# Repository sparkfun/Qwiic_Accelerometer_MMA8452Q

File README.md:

Qwiic Accelerometer - MMA8452Q
========================================

[*SEN-14587*](https://www.sparkfun.com/products/14587)

The Qwiic Accelerometer makes it extremely easy to get playing with tilt, acceleration, and movement sensing. Plug a [Qwiic Shield](https://www.sparkfun.com/search/results?term=qwiic) onto your platform of choice, plug the Qwiic Accelerometer onto the shield and start sensing! 

The Qwiic Accelerometer - MMA8452Q is a smart low-power, three-axis, MEMS accelerometer with 12 bits of resolution. This accelerometer is packed with embedded functions with flexible user programmable options, configurable to two interrupt pins. Embedded interrupt functions allow for overall power savings relieving the host processor from continuously polling data.

The MMA8452Q has user selectable full scales of ±2g/±4g/±8g with high pass filtered data as well as non filtered data available real-time. The device can be configured to generate inertial wake-up interrupt signals from any combination of the configurable embedded functions allowing the MMA8452Q to monitor events and remain in a low power mode during periods of inactivity.

Documentation
--------------
* **Library GitHub Repo**
  * **[Arduino Library](https://github.com/sparkfun/SparkFun_MMA8452Q_Arduino_Library/tree/master)** - Arduino library for MMA8452Q.
  * **[Photon Library](https://github.com/sparkfun/SparkFun_MMA8452Q_Particle_Library)** - Photon library for MMA8452Q.
* **[Hookup Guide](https://learn.sparkfun.com/tutorials/qwiic-accelerometer-mma8452q-hookup-guide)** - Basic hookup guide for the MMA8452Q Breakout Board.
* **[Qwiic System](http://www.sparkfun.com/qwiic)** - The Qwiic system enables fast and solderless connection between popular platforms and various sensors and actuators.

Product Versions
----------------
* [SEN-14587](https://www.sparkfun.com/products/14587)
* [SPX-14248](https://www.sparkfun.com/products/14248)

License Information
-------------------

This product is _**open source**_!

Please review the LICENSE.md file for license information.

If you have any questions or concerns on licensing, please contact techsupport@sparkfun.com.

Distributed as-is; no warranty is given.

- Your friends at SparkFun.

_<COLLABORATION CREDIT>_

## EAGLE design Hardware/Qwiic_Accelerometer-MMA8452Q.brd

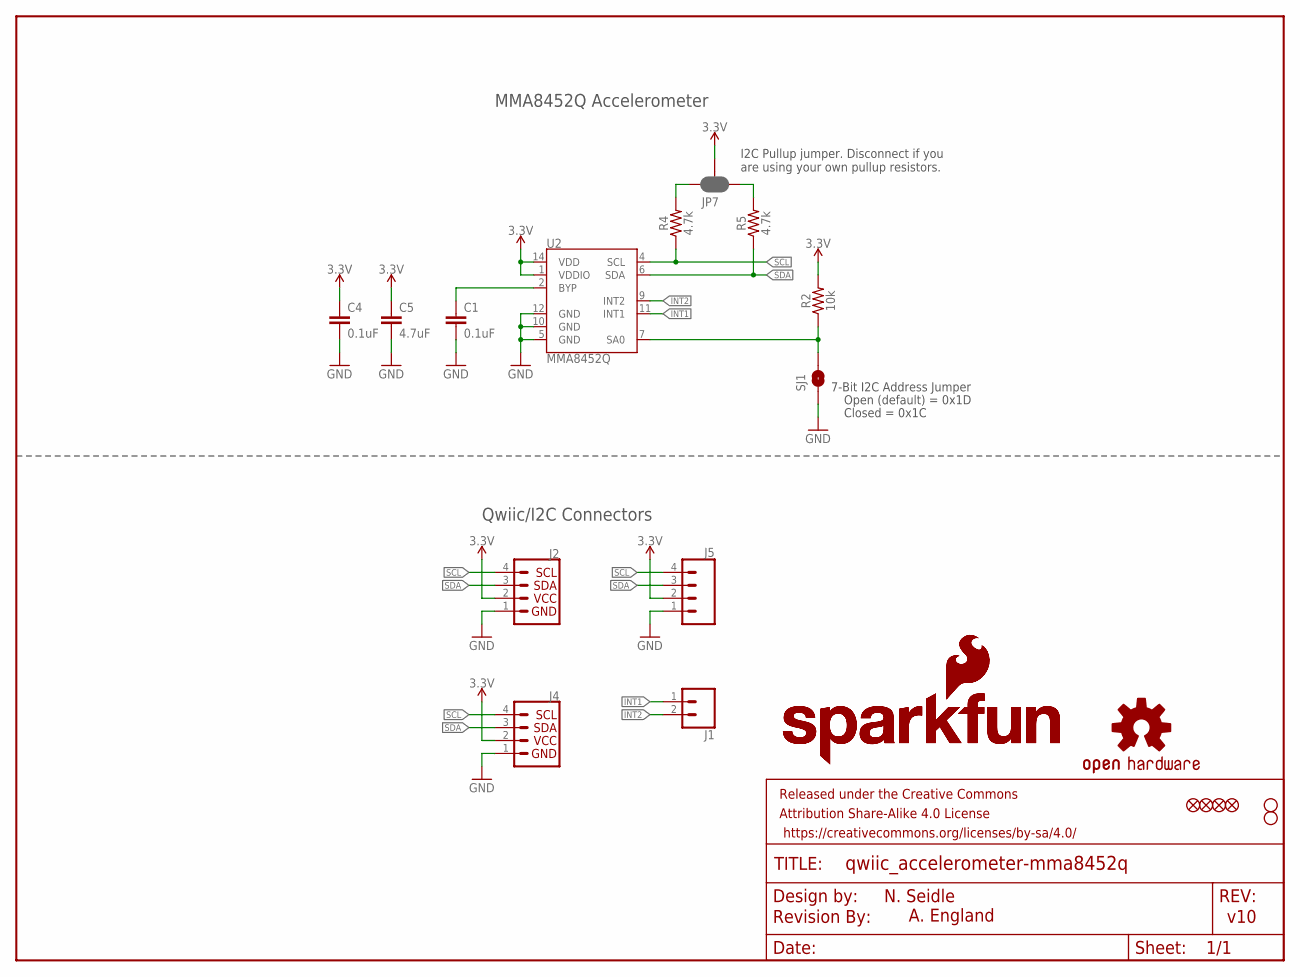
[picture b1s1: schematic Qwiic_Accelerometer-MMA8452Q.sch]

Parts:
C1, C4: 0.1uF; 0603
C5: 4.7uF; 0603
FRAME1: FRAME-LETTER; CREATIVE_COMMONS
J1: CONN_021X02_NO_SILK; 1X02_NO_SILK
J2, J4: QWIIC_CONNECTORJS-1MM; 1X04_1MM_RA
J5: CONN_041X04_NO_SILK; 1X04_NO_SILK
JP1, JP2, JP5, JP6: FIDUCIALUFIDUCIAL; MICRO-FIDUCIAL
JP3, JP4: STAND-OFF
JP7: JUMPER-SMT_3_2-NC_PASTE_SILK; SMT-JUMPER_3_2-NC_PASTE_SILK
LOGO1: OSHW-LOGOMINI; OSHW-LOGO-MINI
LOGO2, LOGO3: SFE_LOGO_NAME_FLAME.1_INCH; SFE_LOGO_NAME_FLAME_.1
LOGO4: REVISION
R2: 10k; 0603
R4, R5: 4.7k; 0603
SJ1: SOLDERJUMPERNO; SJ_2S-NO
U2: MMA8452Q; QFN-16

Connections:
3.3V: C4.1, C5.1, J2.2, J4.2, J5.2, JP7.2, R2.2, U2.1 (VDDIO), U2.14 (VDD)
BYP: C1.1, U2.2 (BYP)
GND: C1.2, C4.2, C5.2, J2.1, J4.1, J5.1, SJ1.1, U2.5 (GND), U2.10 (GND), U2.12 (GND)
INT1: J1.1, U2.11 (INT1)
INT2: J1.2, U2.9 (INT2)
unnamed: JP7.1, R5.2
unnamed: JP7.3, R4.2
SA0: R2.1, SJ1.2, U2.7 (SA0)
SCL: J2.4, J4.4, J5.4, R4.1, U2.4 (SCL)
SDA: J2.3, J4.3, J5.3, R5.1, U2.6 (SDA)

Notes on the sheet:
7-Bit I2C Address Jumper
Closed = 0x1C
Open (default) = 0x1D
N. Seidle
v10
A. England
MMA8452Q Accelerometer
Qwiic/I2C Connectors
I2C Pullup jumper. Disconnect if you are using your own pullup resistors.

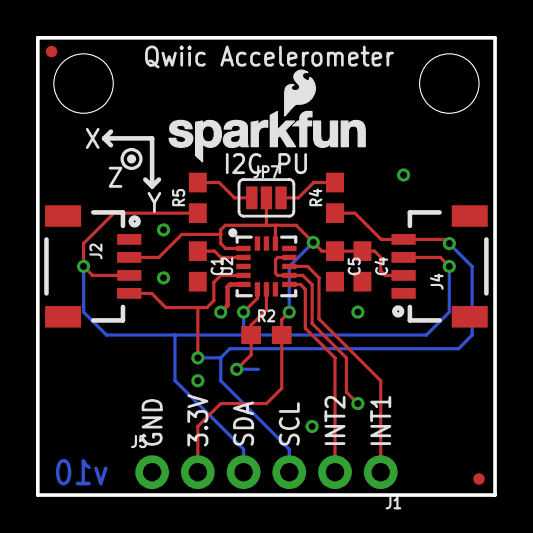
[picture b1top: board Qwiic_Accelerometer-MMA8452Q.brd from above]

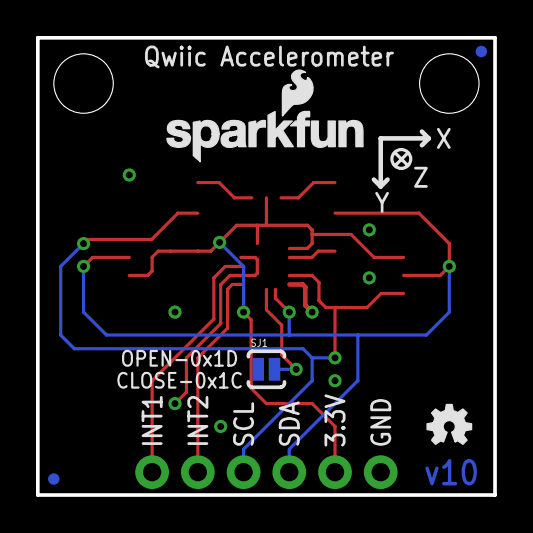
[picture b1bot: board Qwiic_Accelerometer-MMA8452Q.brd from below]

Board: 2 copper layers, 25.4 x 25.4 mm, 24 parts (5 on the bottom side), 10 nets.

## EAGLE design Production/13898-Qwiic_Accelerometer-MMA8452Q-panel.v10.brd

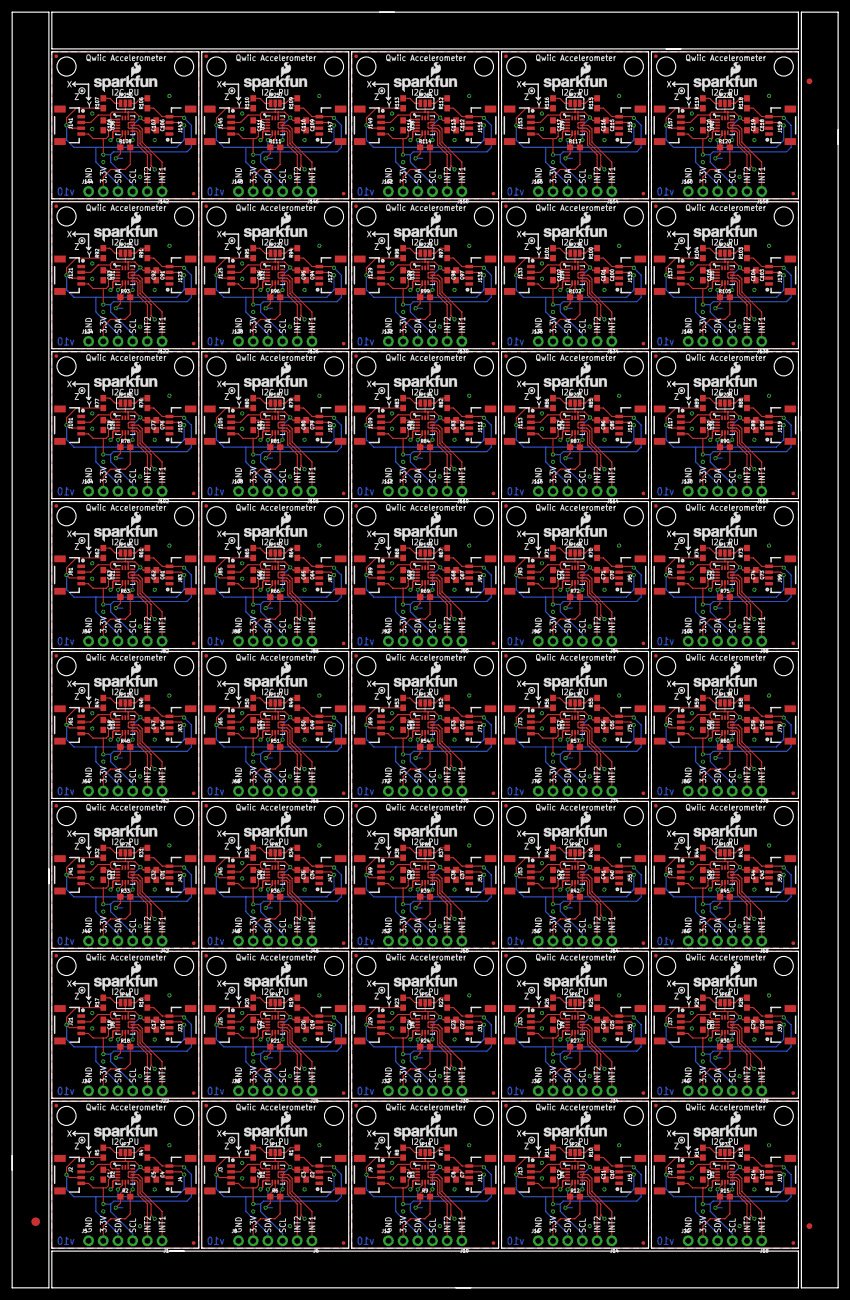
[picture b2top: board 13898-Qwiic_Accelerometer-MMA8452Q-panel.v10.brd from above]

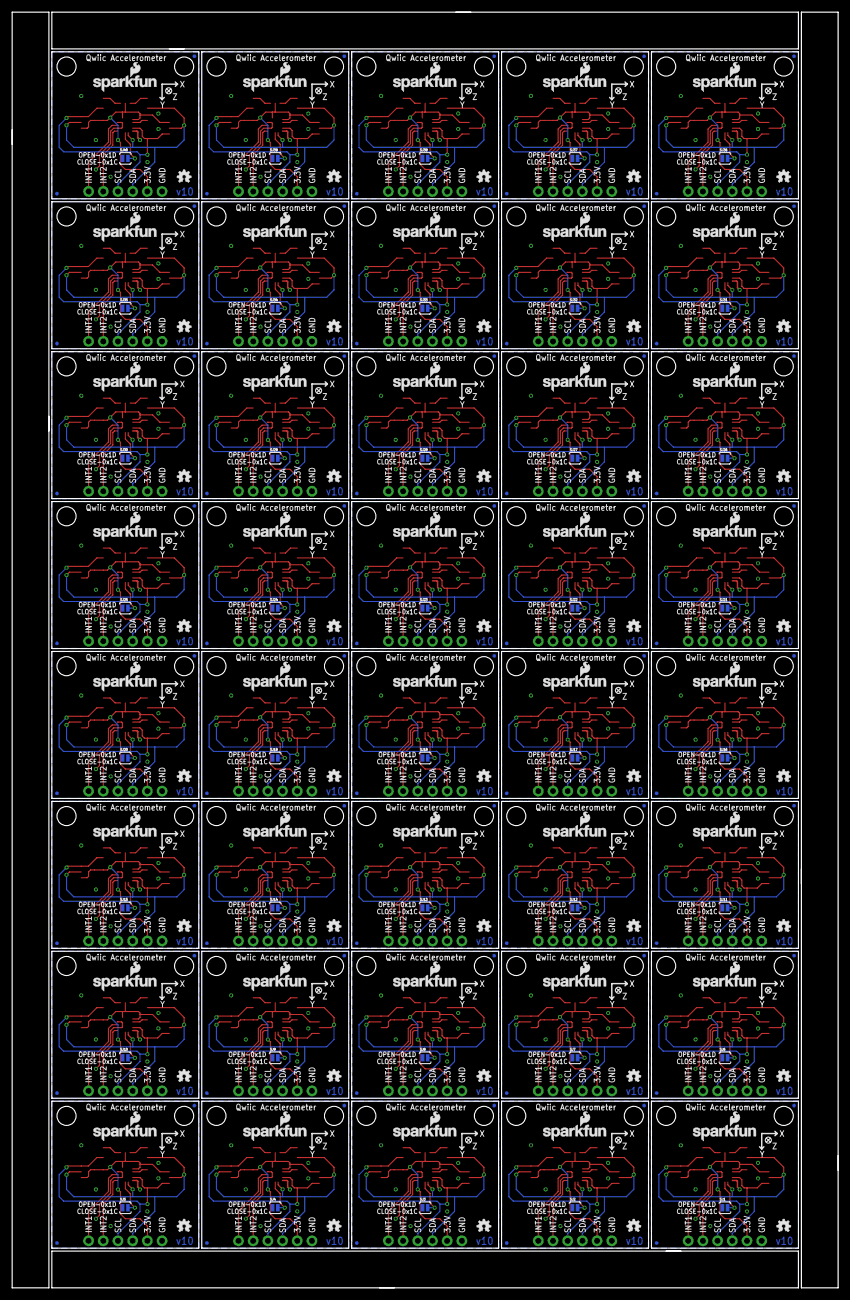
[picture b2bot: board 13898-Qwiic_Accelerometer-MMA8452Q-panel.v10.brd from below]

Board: 2 copper layers, 142.7 x 220.5 mm, 883 parts (200 on the bottom side), 400 nets.

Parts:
C1, C2, C4, C6, C7, C9, C10, C12, C13, C15, C16, C18, C19, C21, C22, C24, C25, C27, C28, C30, C31, C33, C34, C36, C37, C39, C40, C42, C43, C45, C46, C48, C49, C51, C52, C54, C55, C57, C58, C60, C61, C63, C64, C66, C67, C69, C70, C72, C73, C75, C76, C78, C79, C81, C82, C84, C85, C87, C88, C90, C91, C93, C94, C96, C97, C99, C100, C102, C103, C105, C106, C108, C109, C111, C112, C114, C115, C117, C118, C120: 0.1uF; 0603
C3, C5, C8, C11, C14, C17, C20, C23, C26, C29, C32, C35, C38, C41, C44, C47, C50, C53, C56, C59, C62, C65, C68, C71, C74, C77, C80, C83, C86, C89, C92, C95, C98, C101, C104, C107, C110, C113, C116, C119: 4.7uF; 0603
E$1: FIDUCIAL-1.5X3
E$7, E$8: FIDUCIAL-1X2
J1, J6, J10, J14, J18, J22, J26, J30, J34, J38, J42, J46, J50, J54, J58, J62, J66, J70, J74, J78, J82, J86, J90, J94, J98, J102, J106, J110, J114, J118, J122, J126, J130, J134, J138, J142, J146, J150, J154, J158: 1X02_NO_SILK
J2, J3, J4, J7, J9, J11, J13, J15, J17, J19, J21, J23, J25, J27, J29, J31, J33, J35, J37, J39, J41, J43, J45, J47, J49, J51, J53, J55, J57, J59, J61, J63, J65, J67, J69, J71, J73, J75, J77, J79, J81, J83, J85, J87, J89, J91, J93, J95, J97, J99, J101, J103, J105, J107, J109, J111, J113, J115, J117, J119, J121, J123, J125, J127, J129, J131, J133, J135, J137, J139, J141, J143, J145, J147, J149, J151, J153, J155, J157, J159: 1X04_1MM_RA
J5, J8, J12, J16, J20, J24, J28, J32, J36, J40, J44, J48, J52, J56, J60, J64, J68, J72, J76, J80, J84, J88, J92, J96, J100, J104, J108, J112, J116, J120, J124, J128, J132, J136, J140, J144, J148, J152, J156, J160: 1X04_NO_SILK
JP1, JP2, JP5, JP6, JP10, JP11, JP13, JP14, JP17, JP18, JP20, JP21, JP24, JP25, JP27, JP28, JP31, JP32, JP34, JP35, JP38, JP39, JP41, JP42, JP45, JP46, JP48, JP49, JP52, JP53, JP55, JP56, JP59, JP60, JP62, JP63, JP66, JP67, JP69, JP70, JP73, JP74, JP76, JP77, JP80, JP81, JP83, JP84, JP87, JP88, JP90, JP91, JP94, JP95, JP97, JP98, JP101, JP102, JP104, JP105, JP108, JP109, JP111, JP112, JP115, JP116, JP118, JP119, JP122, JP123, JP125, JP126, JP129, JP130, JP132, JP133, JP136, JP137, JP139, JP140, JP143, JP144, JP146, JP147, JP150, JP151, JP153, JP154, JP157, JP158, JP160, JP161, JP164, JP165, JP167, JP168, JP171, JP172, JP174, JP175, JP178, JP179, JP181, JP182, JP185, JP186, JP188, JP189, JP192, JP193, JP195, JP196, JP199, JP200, JP202, JP203, JP206, JP207, JP209, JP210, JP213, JP214, JP216, JP217, JP220, JP221, JP223, JP224, JP227, JP228, JP230, JP231, JP234, JP235, JP237, JP238, JP241, JP242, JP244, JP245, JP248, JP249, JP251, JP252, JP255, JP256, JP258, JP259, JP262, JP263, JP265, JP266, JP269, JP270, JP272, JP273, JP276, JP277, JP279, JP280: FIDUCIALUFIDUCIAL; MICRO-FIDUCIAL
JP3, JP4, JP8, JP9, JP15, JP16, JP22, JP23, JP29, JP30, JP36, JP37, JP43, JP44, JP50, JP51, JP57, JP58, JP64, JP65, JP71, JP72, JP78, JP79, JP85, JP86, JP92, JP93, JP99, JP100, JP106, JP107, JP113, JP114, JP120, JP121, JP127, JP128, JP134, JP135, JP141, JP142, JP148, JP149, JP155, JP156, JP162, JP163, JP169, JP170, JP176, JP177, JP183, JP184, JP190, JP191, JP197, JP198, JP204, JP205, JP211, JP212, JP218, JP219, JP225, JP226, JP232, JP233, JP239, JP240, JP246, JP247, JP253, JP254, JP260, JP261, JP267, JP268, JP274, JP275: STAND-OFF
JP7, JP12, JP19, JP26, JP33, JP40, JP47, JP54, JP61, JP68, JP75, JP82, JP89, JP96, JP103, JP110, JP117, JP124, JP131, JP138, JP145, JP152, JP159, JP166, JP173, JP180, JP187, JP194, JP201, JP208, JP215, JP222, JP229, JP236, JP243, JP250, JP257, JP264, JP271, JP278: SMT-JUMPER_3_2-NC_PASTE_SILK
LOGO1, LOGO4, LOGO7, LOGO10, LOGO13, LOGO16, LOGO19, LOGO22, LOGO25, LOGO28, LOGO31, LOGO34, LOGO37, LOGO40, LOGO43, LOGO46, LOGO49, LOGO52, LOGO55, LOGO58, LOGO61, LOGO64, LOGO67, LOGO70, LOGO73, LOGO76, LOGO79, LOGO82, LOGO85, LOGO88, LOGO91, LOGO94, LOGO97, LOGO100, LOGO103, LOGO106, LOGO109, LOGO112, LOGO115, LOGO118: OSHW-LOGOMINI; OSHW-LOGO-MINI
LOGO2, LOGO3, LOGO5, LOGO6, LOGO8, LOGO9, LOGO11, LOGO12, LOGO14, LOGO15, LOGO17, LOGO18, LOGO20, LOGO21, LOGO23, LOGO24, LOGO26, LOGO27, LOGO29, LOGO30, LOGO32, LOGO33, LOGO35, LOGO36, LOGO38, LOGO39, LOGO41, LOGO42, LOGO44, LOGO45, LOGO47, LOGO48, LOGO50, LOGO51, LOGO53, LOGO54, LOGO56, LOGO57, LOGO59, LOGO60, LOGO62, LOGO63, LOGO65, LOGO66, LOGO68, LOGO69, LOGO71, LOGO72, LOGO74, LOGO75, LOGO77, LOGO78, LOGO80, LOGO81, LOGO83, LOGO84, LOGO86, LOGO87, LOGO89, LOGO90, LOGO92, LOGO93, LOGO95, LOGO96, LOGO98, LOGO99, LOGO101, LOGO102, LOGO104, LOGO105, LOGO107, LOGO108, LOGO110, LOGO111, LOGO113, LOGO114, LOGO116, LOGO117, LOGO119, LOGO120: SFE_LOGO_NAME_FLAME.1_INCH; SFE_LOGO_NAME_FLAME_.1
R1, R3, R4, R5, R7, R8, R10, R11, R13, R14, R16, R17, R19, R20, R22, R23, R25, R26, R28, R29, R31, R32, R34, R35, R37, R38, R40, R41, R43, R44, R46, R47, R49, R50, R52, R53, R55, R56, R58, R59, R61, R62, R64, R65, R67, R68, R70, R71, R73, R74, R76, R77, R79, R80, R82, R83, R85, R86, R88, R89, R91, R92, R94, R95, R97, R98, R100, R101, R103, R104, R106, R107, R109, R110, R112, R113, R115, R116, R118, R119: 4.7k; 0603
R2, R6, R9, R12, R15, R18, R21, R24, R27, R30, R33, R36, R39, R42, R45, R48, R51, R54, R57, R60, R63, R66, R69, R72, R75, R78, R81, R84, R87, R90, R93, R96, R99, R102, R105, R108, R111, R114, R117, R120: 10k; 0603
SJ1, SJ2, SJ3, SJ4, SJ5, SJ6, SJ7, SJ8, SJ9, SJ10, SJ11, SJ12, SJ13, SJ14, SJ15, SJ16, SJ17, SJ18, SJ19, SJ20, SJ21, SJ22, SJ23, SJ24, SJ25, SJ26, SJ27, SJ28, SJ29, SJ30, SJ31, SJ32, SJ33, SJ34, SJ35, SJ36, SJ37, SJ38, SJ39, SJ40: SJ_2S-NO
U1, U2, U3, U4, U5, U6, U7, U8, U9, U10, U11, U12, U13, U14, U15, U16, U17, U18, U19, U20, U21, U22, U23, U24, U25, U26, U27, U28, U29, U30, U31, U32, U33, U34, U35, U36, U37, U38, U39, U40: MMA8452Q; QFN-16

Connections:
3.3V: C4.1, C5.1, J2.2, J4.2, J5.2, JP7.2, R2.2, U2.1, U2.14
3.3V1: C2.1, C3.1, J3.2, J7.2, J8.2, JP12.2, R6.2, U1.1, U1.14
3.3V2: C7.1, C8.1, J9.2, J11.2, J12.2, JP19.2, R9.2, U3.1, U3.14
3.3V3: C10.1, C11.1, J13.2, J15.2, J16.2, JP26.2, R12.2, U4.1, U4.14
3.3V4: C13.1, C14.1, J17.2, J19.2, J20.2, JP33.2, R15.2, U5.1, U5.14
3.3V5: C16.1, C17.1, J21.2, J23.2, J24.2, JP40.2, R18.2, U6.1, U6.14
3.3V6: C19.1, C20.1, J25.2, J27.2, J28.2, JP47.2, R21.2, U7.1, U7.14
3.3V7: C22.1, C23.1, J29.2, J31.2, J32.2, JP54.2, R24.2, U8.1, U8.14
3.3V8: C25.1, C26.1, J33.2, J35.2, J36.2, JP61.2, R27.2, U9.1, U9.14
3.3V9: C28.1, C29.1, J37.2, J39.2, J40.2, JP68.2, R30.2, U10.1, U10.14
3.3V10: C31.1, C32.1, J41.2, J43.2, J44.2, JP75.2, R33.2, U11.1, U11.14
3.3V11: C34.1, C35.1, J45.2, J47.2, J48.2, JP82.2, R36.2, U12.1, U12.14
3.3V12: C37.1, C38.1, J49.2, J51.2, J52.2, JP89.2, R39.2, U13.1, U13.14
3.3V13: C40.1, C41.1, J53.2, J55.2, J56.2, JP96.2, R42.2, U14.1, U14.14
3.3V14: C43.1, C44.1, J57.2, J59.2, J60.2, JP103.2, R45.2, U15.1, U15.14
3.3V15: C46.1, C47.1, J61.2, J63.2, J64.2, JP110.2, R48.2, U16.1, U16.14
3.3V16: C49.1, C50.1, J65.2, J67.2, J68.2, JP117.2, R51.2, U17.1, U17.14
3.3V17: C52.1, C53.1, J69.2, J71.2, J72.2, JP124.2, R54.2, U18.1, U18.14
3.3V18: C55.1, C56.1, J73.2, J75.2, J76.2, JP131.2, R57.2, U19.1, U19.14
3.3V19: C58.1, C59.1, J77.2, J79.2, J80.2, JP138.2, R60.2, U20.1, U20.14
3.3V20: C61.1, C62.1, J81.2, J83.2, J84.2, JP145.2, R63.2, U21.1, U21.14
3.3V21: C64.1, C65.1, J85.2, J87.2, J88.2, JP152.2, R66.2, U22.1, U22.14
3.3V22: C67.1, C68.1, J89.2, J91.2, J92.2, JP159.2, R69.2, U23.1, U23.14
3.3V23: C70.1, C71.1, J93.2, J95.2, J96.2, JP166.2, R72.2, U24.1, U24.14
3.3V24: C73.1, C74.1, J97.2, J99.2, J100.2, JP173.2, R75.2, U25.1, U25.14
3.3V25: C76.1, C77.1, J101.2, J103.2, J104.2, JP180.2, R78.2, U26.1, U26.14
3.3V26: C79.1, C80.1, J105.2, J107.2, J108.2, JP187.2, R81.2, U27.1, U27.14
3.3V27: C82.1, C83.1, J109.2, J111.2, J112.2, JP194.2, R84.2, U28.1, U28.14
3.3V28: C85.1, C86.1, J113.2, J115.2, J116.2, JP201.2, R87.2, U29.1, U29.14
3.3V29: C88.1, C89.1, J117.2, J119.2, J120.2, JP208.2, R90.2, U30.1, U30.14
3.3V30: C91.1, C92.1, J121.2, J123.2, J124.2, JP215.2, R93.2, U31.1, U31.14
3.3V31: C94.1, C95.1, J125.2, J127.2, J128.2, JP222.2, R96.2, U32.1, U32.14
3.3V32: C97.1, C98.1, J129.2, J131.2, J132.2, JP229.2, R99.2, U33.1, U33.14
3.3V33: C100.1, C101.1, J133.2, J135.2, J136.2, JP236.2, R102.2, U34.1, U34.14
3.3V34: C103.1, C104.1, J137.2, J139.2, J140.2, JP243.2, R105.2, U35.1, U35.14
3.3V35: C106.1, C107.1, J141.2, J143.2, J144.2, JP250.2, R108.2, U36.1, U36.14
3.3V36: C109.1, C110.1, J145.2, J147.2, J148.2, JP257.2, R111.2, U37.1, U37.14
3.3V37: C112.1, C113.1, J149.2, J151.2, J152.2, JP264.2, R114.2, U38.1, U38.14
3.3V38: C115.1, C116.1, J153.2, J155.2, J156.2, JP271.2, R117.2, U39.1, U39.14
3.3V39: C118.1, C119.1, J157.2, J159.2, J160.2, JP278.2, R120.2, U40.1, U40.14
BYP: C1.1, U2.2
BYP1: C6.1, U1.2
BYP2: C9.1, U3.2
BYP3: C12.1, U4.2
BYP4: C15.1, U5.2
BYP5: C18.1, U6.2
BYP6: C21.1, U7.2
BYP7: C24.1, U8.2
BYP8: C27.1, U9.2
BYP9: C30.1, U10.2
BYP10: C33.1, U11.2
BYP11: C36.1, U12.2
BYP12: C39.1, U13.2
BYP13: C42.1, U14.2
BYP14: C45.1, U15.2
BYP15: C48.1, U16.2
BYP16: C51.1, U17.2
BYP17: C54.1, U18.2
BYP18: C57.1, U19.2
BYP19: C60.1, U20.2
BYP20: C63.1, U21.2
BYP21: C66.1, U22.2
BYP22: C69.1, U23.2
BYP23: C72.1, U24.2
BYP24: C75.1, U25.2
BYP25: C78.1, U26.2
BYP26: C81.1, U27.2
BYP27: C84.1, U28.2
BYP28: C87.1, U29.2
BYP29: C90.1, U30.2
BYP30: C93.1, U31.2
BYP31: C96.1, U32.2
BYP32: C99.1, U33.2
BYP33: C102.1, U34.2
BYP34: C105.1, U35.2
BYP35: C108.1, U36.2
BYP36: C111.1, U37.2
BYP37: C114.1, U38.2
BYP38: C117.1, U39.2
BYP39: C120.1, U40.2
GND: C1.2, C4.2, C5.2, J2.1, J4.1, J5.1, SJ1.1, U2.5, U2.10, U2.12
GND1: C2.2, C3.2, C6.2, J3.1, J7.1, J8.1, SJ2.1, U1.5, U1.10, U1.12
GND2: C7.2, C8.2, C9.2, J9.1, J11.1, J12.1, SJ3.1, U3.5, U3.10, U3.12
GND3: C10.2, C11.2, C12.2, J13.1, J15.1, J16.1, SJ4.1, U4.5, U4.10, U4.12
GND4: C13.2, C14.2, C15.2, J17.1, J19.1, J20.1, SJ5.1, U5.5, U5.10, U5.12
GND5: C16.2, C17.2, C18.2, J21.1, J23.1, J24.1, SJ6.1, U6.5, U6.10, U6.12
GND6: C19.2, C20.2, C21.2, J25.1, J27.1, J28.1, SJ7.1, U7.5, U7.10, U7.12
GND7: C22.2, C23.2, C24.2, J29.1, J31.1, J32.1, SJ8.1, U8.5, U8.10, U8.12
GND8: C25.2, C26.2, C27.2, J33.1, J35.1, J36.1, SJ9.1, U9.5, U9.10, U9.12
GND9: C28.2, C29.2, C30.2, J37.1, J39.1, J40.1, SJ10.1, U10.5, U10.10, U10.12
GND10: C31.2, C32.2, C33.2, J41.1, J43.1, J44.1, SJ11.1, U11.5, U11.10, U11.12
GND11: C34.2, C35.2, C36.2, J45.1, J47.1, J48.1, SJ12.1, U12.5, U12.10, U12.12
GND12: C37.2, C38.2, C39.2, J49.1, J51.1, J52.1, SJ13.1, U13.5, U13.10, U13.12
GND13: C40.2, C41.2, C42.2, J53.1, J55.1, J56.1, SJ14.1, U14.5, U14.10, U14.12
GND14: C43.2, C44.2, C45.2, J57.1, J59.1, J60.1, SJ15.1, U15.5, U15.10, U15.12
GND15: C46.2, C47.2, C48.2, J61.1, J63.1, J64.1, SJ16.1, U16.5, U16.10, U16.12
GND16: C49.2, C50.2, C51.2, J65.1, J67.1, J68.1, SJ17.1, U17.5, U17.10, U17.12
GND17: C52.2, C53.2, C54.2, J69.1, J71.1, J72.1, SJ18.1, U18.5, U18.10, U18.12
GND18: C55.2, C56.2, C57.2, J73.1, J75.1, J76.1, SJ19.1, U19.5, U19.10, U19.12
GND19: C58.2, C59.2, C60.2, J77.1, J79.1, J80.1, SJ20.1, U20.5, U20.10, U20.12
GND20: C61.2, C62.2, C63.2, J81.1, J83.1, J84.1, SJ21.1, U21.5, U21.10, U21.12
GND21: C64.2, C65.2, C66.2, J85.1, J87.1, J88.1, SJ22.1, U22.5, U22.10, U22.12
GND22: C67.2, C68.2, C69.2, J89.1, J91.1, J92.1, SJ23.1, U23.5, U23.10, U23.12
GND23: C70.2, C71.2, C72.2, J93.1, J95.1, J96.1, SJ24.1, U24.5, U24.10, U24.12
GND24: C73.2, C74.2, C75.2, J97.1, J99.1, J100.1, SJ25.1, U25.5, U25.10, U25.12
GND25: C76.2, C77.2, C78.2, J101.1, J103.1, J104.1, SJ26.1, U26.5, U26.10, U26.12
GND26: C79.2, C80.2, C81.2, J105.1, J107.1, J108.1, SJ27.1, U27.5, U27.10, U27.12
GND27: C82.2, C83.2, C84.2, J109.1, J111.1, J112.1, SJ28.1, U28.5, U28.10, U28.12
GND28: C85.2, C86.2, C87.2, J113.1, J115.1, J116.1, SJ29.1, U29.5, U29.10, U29.12
GND29: C88.2, C89.2, C90.2, J117.1, J119.1, J120.1, SJ30.1, U30.5, U30.10, U30.12
GND30: C91.2, C92.2, C93.2, J121.1, J123.1, J124.1, SJ31.1, U31.5, U31.10, U31.12
GND31: C94.2, C95.2, C96.2, J125.1, J127.1, J128.1, SJ32.1, U32.5, U32.10, U32.12
GND32: C97.2, C98.2, C99.2, J129.1, J131.1, J132.1, SJ33.1, U33.5, U33.10, U33.12
GND33: C100.2, C101.2, C102.2, J133.1, J135.1, J136.1, SJ34.1, U34.5, U34.10, U34.12
GND34: C103.2, C104.2, C105.2, J137.1, J139.1, J140.1, SJ35.1, U35.5, U35.10, U35.12
GND35: C106.2, C107.2, C108.2, J141.1, J143.1, J144.1, SJ36.1, U36.5, U36.10, U36.12
GND36: C109.2, C110.2, C111.2, J145.1, J147.1, J148.1, SJ37.1, U37.5, U37.10, U37.12
GND37: C112.2, C113.2, C114.2, J149.1, J151.1, J152.1, SJ38.1, U38.5, U38.10, U38.12
GND38: C115.2, C116.2, C117.2, J153.1, J155.1, J156.1, SJ39.1, U39.5, U39.10, U39.12
GND39: C118.2, C119.2, C120.2, J157.1, J159.1, J160.1, SJ40.1, U40.5, U40.10, U40.12
INT1: J1.1, U2.11
INT2: J1.2, U2.9
INT3: J6.2, U1.9
INT4: J6.1, U1.11
INT5: J10.2, U3.9
INT6: J10.1, U3.11
INT7: J14.2, U4.9
INT8: J14.1, U4.11
INT9: J18.2, U5.9
INT10: J18.1, U5.11
INT11: J22.2, U6.9
INT12: J22.1, U6.11
INT13: J26.2, U7.9
INT14: J26.1, U7.11
INT15: J30.2, U8.9
INT16: J30.1, U8.11
INT17: J34.2, U9.9
INT18: J34.1, U9.11
INT19: J38.2, U10.9
INT20: J38.1, U10.11
INT21: J42.2, U11.9
INT22: J42.1, U11.11
INT23: J46.2, U12.9
INT24: J46.1, U12.11
INT25: J50.2, U13.9
INT26: J50.1, U13.11
INT27: J54.2, U14.9
INT28: J54.1, U14.11
INT29: J58.2, U15.9
INT30: J58.1, U15.11
INT31: J62.2, U16.9
INT32: J62.1, U16.11
INT33: J66.2, U17.9
INT34: J66.1, U17.11
INT35: J70.2, U18.9
INT36: J70.1, U18.11
INT37: J74.2, U19.9
INT38: J74.1, U19.11
INT39: J78.2, U20.9
INT40: J78.1, U20.11
INT41: J82.2, U21.9
INT42: J82.1, U21.11
INT43: J86.2, U22.9
INT44: J86.1, U22.11
INT45: J90.2, U23.9
INT46: J90.1, U23.11
INT47: J94.2, U24.9
INT48: J94.1, U24.11
INT49: J98.2, U25.9
INT50: J98.1, U25.11
INT51: J102.2, U26.9
INT52: J102.1, U26.11
INT53: J106.2, U27.9
INT54: J106.1, U27.11
INT55: J110.2, U28.9
INT56: J110.1, U28.11
INT57: J114.2, U29.9
INT58: J114.1, U29.11
INT59: J118.2, U30.9
INT60: J118.1, U30.11
INT61: J122.2, U31.9
INT62: J122.1, U31.11
INT63: J126.2, U32.9
INT64: J126.1, U32.11
INT65: J130.2, U33.9
INT66: J130.1, U33.11
INT67: J134.2, U34.9
INT68: J134.1, U34.11
INT69: J138.2, U35.9
INT70: J138.1, U35.11
INT71: J142.2, U36.9
INT72: J142.1, U36.11
INT73: J146.2, U37.9
INT74: J146.1, U37.11
INT75: J150.2, U38.9
INT76: J150.1, U38.11
INT77: J154.2, U39.9
INT78: J154.1, U39.11
INT79: J158.2, U40.9
INT80: J158.1, U40.11
unnamed: JP7.1, R5.2
unnamed: JP7.3, R4.2
unnamed: JP12.1, R3.2
unnamed: JP12.3, R1.2
unnamed: JP19.1, R8.2
unnamed: JP19.3, R7.2
unnamed: JP26.1, R11.2
unnamed: JP26.3, R10.2
unnamed: JP33.1, R14.2
unnamed: JP33.3, R13.2
unnamed: JP40.1, R17.2
unnamed: JP40.3, R16.2
unnamed: JP47.1, R20.2
unnamed: JP47.3, R19.2
unnamed: JP54.1, R23.2
unnamed: JP54.3, R22.2
unnamed: JP61.1, R26.2
unnamed: JP61.3, R25.2
unnamed: JP68.1, R29.2
unnamed: JP68.3, R28.2
unnamed: JP75.1, R32.2
unnamed: JP75.3, R31.2
unnamed: JP82.1, R35.2
unnamed: JP82.3, R34.2
unnamed: JP89.1, R38.2
unnamed: JP89.3, R37.2
unnamed: JP96.1, R41.2
unnamed: JP96.3, R40.2
unnamed: JP103.1, R44.2
unnamed: JP103.3, R43.2
unnamed: JP110.1, R47.2
unnamed: JP110.3, R46.2
unnamed: JP117.1, R50.2
unnamed: JP117.3, R49.2
unnamed: JP124.1, R53.2
unnamed: JP124.3, R52.2
unnamed: JP131.1, R56.2
unnamed: JP131.3, R55.2
unnamed: JP138.1, R59.2
unnamed: JP138.3, R58.2
unnamed: JP145.1, R62.2
unnamed: JP145.3, R61.2
unnamed: JP152.1, R65.2
unnamed: JP152.3, R64.2
unnamed: JP159.1, R68.2
unnamed: JP159.3, R67.2
unnamed: JP166.1, R71.2
unnamed: JP166.3, R70.2
unnamed: JP173.1, R74.2
unnamed: JP173.3, R73.2
unnamed: JP180.1, R77.2
unnamed: JP180.3, R76.2
unnamed: JP187.1, R80.2
unnamed: JP187.3, R79.2
unnamed: JP194.1, R83.2
unnamed: JP194.3, R82.2
unnamed: JP201.1, R86.2
unnamed: JP201.3, R85.2
unnamed: JP208.1, R89.2
unnamed: JP208.3, R88.2
unnamed: JP215.1, R92.2
unnamed: JP215.3, R91.2
unnamed: JP222.1, R95.2
unnamed: JP222.3, R94.2
unnamed: JP229.1, R98.2
unnamed: JP229.3, R97.2
unnamed: JP236.1, R101.2
unnamed: JP236.3, R100.2
unnamed: JP243.1, R104.2
unnamed: JP243.3, R103.2
unnamed: JP250.1, R107.2
unnamed: JP250.3, R106.2
unnamed: JP257.1, R110.2
unnamed: JP257.3, R109.2
unnamed: JP264.1, R113.2
unnamed: JP264.3, R112.2
unnamed: JP271.1, R116.2
unnamed: JP271.3, R115.2
unnamed: JP278.1, R119.2
unnamed: JP278.3, R118.2
SA0: R2.1, SJ1.2, U2.7
SA1: R6.1, SJ2.2, U1.7
SA2: R9.1, SJ3.2, U3.7
SA3: R12.1, SJ4.2, U4.7
SA4: R15.1, SJ5.2, U5.7
SA5: R18.1, SJ6.2, U6.7
SA6: R21.1, SJ7.2, U7.7
SA7: R24.1, SJ8.2, U8.7
SA8: R27.1, SJ9.2, U9.7
SA9: R30.1, SJ10.2, U10.7
SA10: R33.1, SJ11.2, U11.7
SA11: R36.1, SJ12.2, U12.7
SA12: R39.1, SJ13.2, U13.7
SA13: R42.1, SJ14.2, U14.7
SA14: R45.1, SJ15.2, U15.7
SA15: R48.1, SJ16.2, U16.7
SA16: R51.1, SJ17.2, U17.7
SA17: R54.1, SJ18.2, U18.7
SA18: R57.1, SJ19.2, U19.7
SA19: R60.1, SJ20.2, U20.7
SA20: R63.1, SJ21.2, U21.7
SA21: R66.1, SJ22.2, U22.7
SA22: R69.1, SJ23.2, U23.7
SA23: R72.1, SJ24.2, U24.7
SA24: R75.1, SJ25.2, U25.7
SA25: R78.1, SJ26.2, U26.7
SA26: R81.1, SJ27.2, U27.7
SA27: R84.1, SJ28.2, U28.7
SA28: R87.1, SJ29.2, U29.7
SA29: R90.1, SJ30.2, U30.7
SA30: R93.1, SJ31.2, U31.7
SA31: R96.1, SJ32.2, U32.7
SA32: R99.1, SJ33.2, U33.7
SA33: R102.1, SJ34.2, U34.7
SA34: R105.1, SJ35.2, U35.7
SA35: R108.1, SJ36.2, U36.7
SA36: R111.1, SJ37.2, U37.7
SA37: R114.1, SJ38.2, U38.7
SA38: R117.1, SJ39.2, U39.7
SA39: R120.1, SJ40.2, U40.7
SCL: J2.4, J4.4, J5.4, R4.1, U2.4
SCL1: J3.4, J7.4, J8.4, R1.1, U1.4
SCL2: J9.4, J11.4, J12.4, R7.1, U3.4
SCL3: J13.4, J15.4, J16.4, R10.1, U4.4
SCL4: J17.4, J19.4, J20.4, R13.1, U5.4
SCL5: J21.4, J23.4, J24.4, R16.1, U6.4
SCL6: J25.4, J27.4, J28.4, R19.1, U7.4
SCL7: J29.4, J31.4, J32.4, R22.1, U8.4
SCL8: J33.4, J35.4, J36.4, R25.1, U9.4
SCL9: J37.4, J39.4, J40.4, R28.1, U10.4
SCL10: J41.4, J43.4, J44.4, R31.1, U11.4
SCL11: J45.4, J47.4, J48.4, R34.1, U12.4
SCL12: J49.4, J51.4, J52.4, R37.1, U13.4
SCL13: J53.4, J55.4, J56.4, R40.1, U14.4
SCL14: J57.4, J59.4, J60.4, R43.1, U15.4
SCL15: J61.4, J63.4, J64.4, R46.1, U16.4
SCL16: J65.4, J67.4, J68.4, R49.1, U17.4
SCL17: J69.4, J71.4, J72.4, R52.1, U18.4
SCL18: J73.4, J75.4, J76.4, R55.1, U19.4
SCL19: J77.4, J79.4, J80.4, R58.1, U20.4
SCL20: J81.4, J83.4, J84.4, R61.1, U21.4
SCL21: J85.4, J87.4, J88.4, R64.1, U22.4
SCL22: J89.4, J91.4, J92.4, R67.1, U23.4
SCL23: J93.4, J95.4, J96.4, R70.1, U24.4
SCL24: J97.4, J99.4, J100.4, R73.1, U25.4
SCL25: J101.4, J103.4, J104.4, R76.1, U26.4
SCL26: J105.4, J107.4, J108.4, R79.1, U27.4
SCL27: J109.4, J111.4, J112.4, R82.1, U28.4
SCL28: J113.4, J115.4, J116.4, R85.1, U29.4
SCL29: J117.4, J119.4, J120.4, R88.1, U30.4
SCL30: J121.4, J123.4, J124.4, R91.1, U31.4
SCL31: J125.4, J127.4, J128.4, R94.1, U32.4
SCL32: J129.4, J131.4, J132.4, R97.1, U33.4
SCL33: J133.4, J135.4, J136.4, R100.1, U34.4
SCL34: J137.4, J139.4, J140.4, R103.1, U35.4
SCL35: J141.4, J143.4, J144.4, R106.1, U36.4
SCL36: J145.4, J147.4, J148.4, R109.1, U37.4
SCL37: J149.4, J151.4, J152.4, R112.1, U38.4
SCL38: J153.4, J155.4, J156.4, R115.1, U39.4
SCL39: J157.4, J159.4, J160.4, R118.1, U40.4
SDA: J2.3, J4.3, J5.3, R5.1, U2.6
SDA1: J3.3, J7.3, J8.3, R3.1, U1.6
SDA2: J9.3, J11.3, J12.3, R8.1, U3.6
SDA3: J13.3, J15.3, J16.3, R11.1, U4.6
SDA4: J17.3, J19.3, J20.3, R14.1, U5.6
SDA5: J21.3, J23.3, J24.3, R17.1, U6.6
SDA6: J25.3, J27.3, J28.3, R20.1, U7.6
SDA7: J29.3, J31.3, J32.3, R23.1, U8.6
SDA8: J33.3, J35.3, J36.3, R26.1, U9.6
SDA9: J37.3, J39.3, J40.3, R29.1, U10.6
SDA10: J41.3, J43.3, J44.3, R32.1, U11.6
SDA11: J45.3, J47.3, J48.3, R35.1, U12.6
SDA12: J49.3, J51.3, J52.3, R38.1, U13.6
SDA13: J53.3, J55.3, J56.3, R41.1, U14.6
SDA14: J57.3, J59.3, J60.3, R44.1, U15.6
SDA15: J61.3, J63.3, J64.3, R47.1, U16.6
SDA16: J65.3, J67.3, J68.3, R50.1, U17.6
SDA17: J69.3, J71.3, J72.3, R53.1, U18.6
SDA18: J73.3, J75.3, J76.3, R56.1, U19.6
SDA19: J77.3, J79.3, J80.3, R59.1, U20.6
SDA20: J81.3, J83.3, J84.3, R62.1, U21.6
SDA21: J85.3, J87.3, J88.3, R65.1, U22.6
SDA22: J89.3, J91.3, J92.3, R68.1, U23.6
SDA23: J93.3, J95.3, J96.3, R71.1, U24.6
SDA24: J97.3, J99.3, J100.3, R74.1, U25.6
SDA25: J101.3, J103.3, J104.3, R77.1, U26.6
SDA26: J105.3, J107.3, J108.3, R80.1, U27.6
SDA27: J109.3, J111.3, J112.3, R83.1, U28.6
SDA28: J113.3, J115.3, J116.3, R86.1, U29.6
SDA29: J117.3, J119.3, J120.3, R89.1, U30.6
SDA30: J121.3, J123.3, J124.3, R92.1, U31.6
SDA31: J125.3, J127.3, J128.3, R95.1, U32.6
SDA32: J129.3, J131.3, J132.3, R98.1, U33.6
SDA33: J133.3, J135.3, J136.3, R101.1, U34.6
SDA34: J137.3, J139.3, J140.3, R104.1, U35.6
SDA35: J141.3, J143.3, J144.3, R107.1, U36.6
SDA36: J145.3, J147.3, J148.3, R110.1, U37.6
SDA37: J149.3, J151.3, J152.3, R113.1, U38.6
SDA38: J153.3, J155.3, J156.3, R116.1, U39.6
SDA39: J157.3, J159.3, J160.3, R119.1, U40.6

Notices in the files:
parts and their libraries:
SparkFun-Resistors: Licensing: Creative Commons ShareAlike 4.0 International - https://creativecommons.org/licenses/by-sa/4.0
SparkFun-Aesthetics: Released under the Creative Commons Attribution Share-Alike 4.0 License
SparkFun-Aesthetics: https://creativecommons.org/licenses/by-sa/4.0
